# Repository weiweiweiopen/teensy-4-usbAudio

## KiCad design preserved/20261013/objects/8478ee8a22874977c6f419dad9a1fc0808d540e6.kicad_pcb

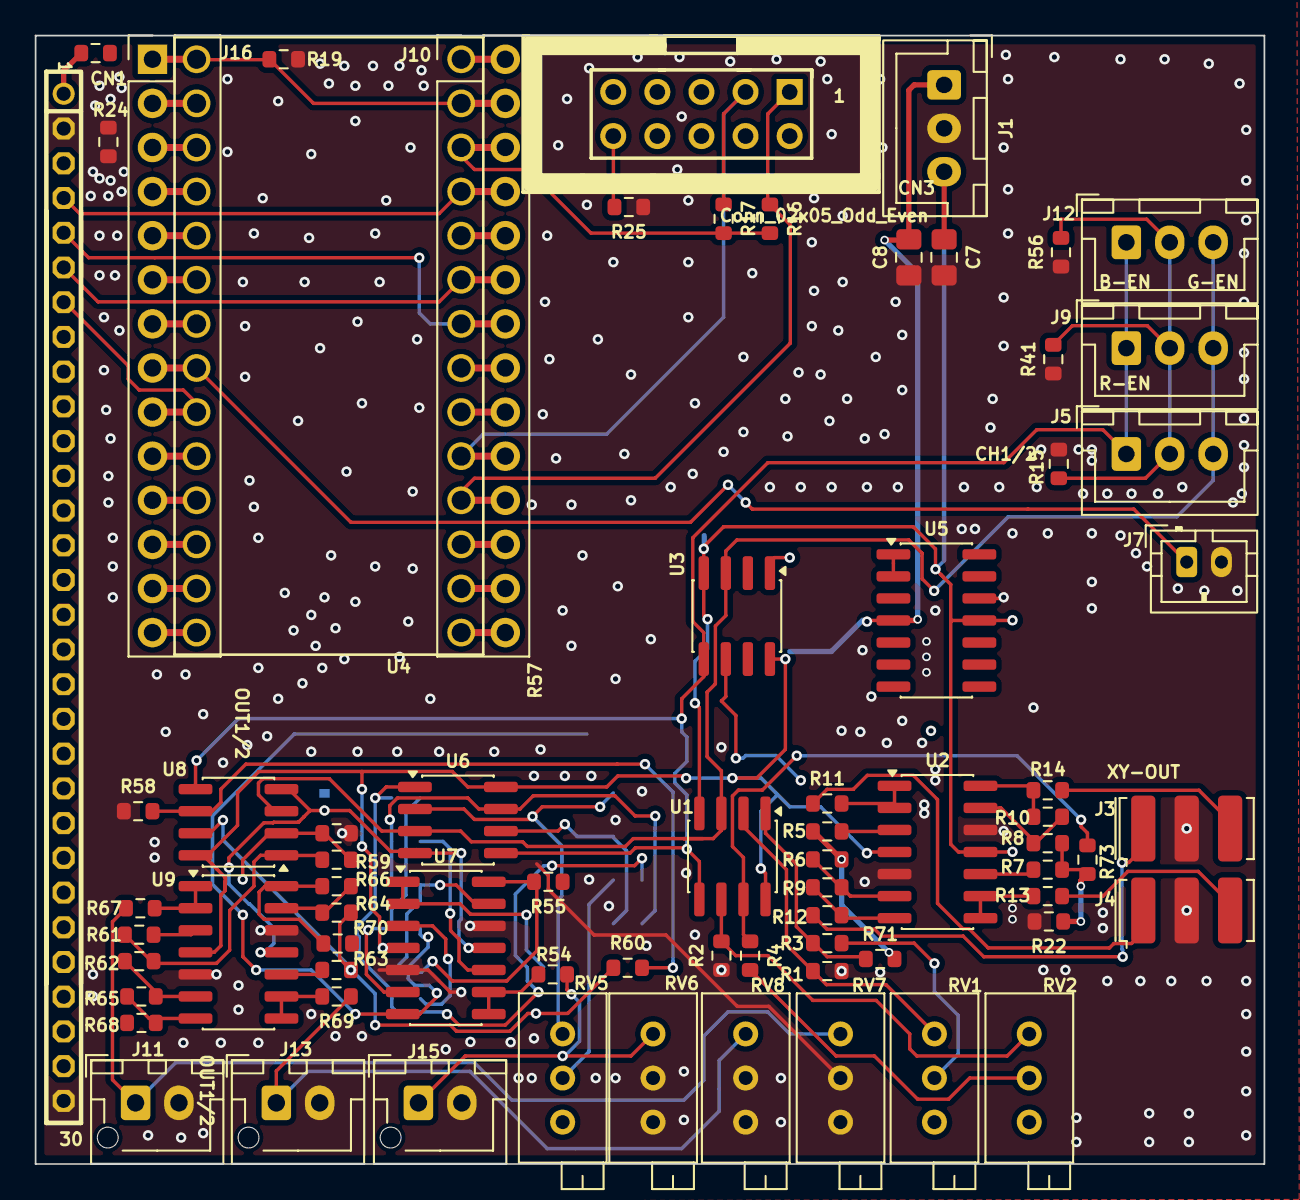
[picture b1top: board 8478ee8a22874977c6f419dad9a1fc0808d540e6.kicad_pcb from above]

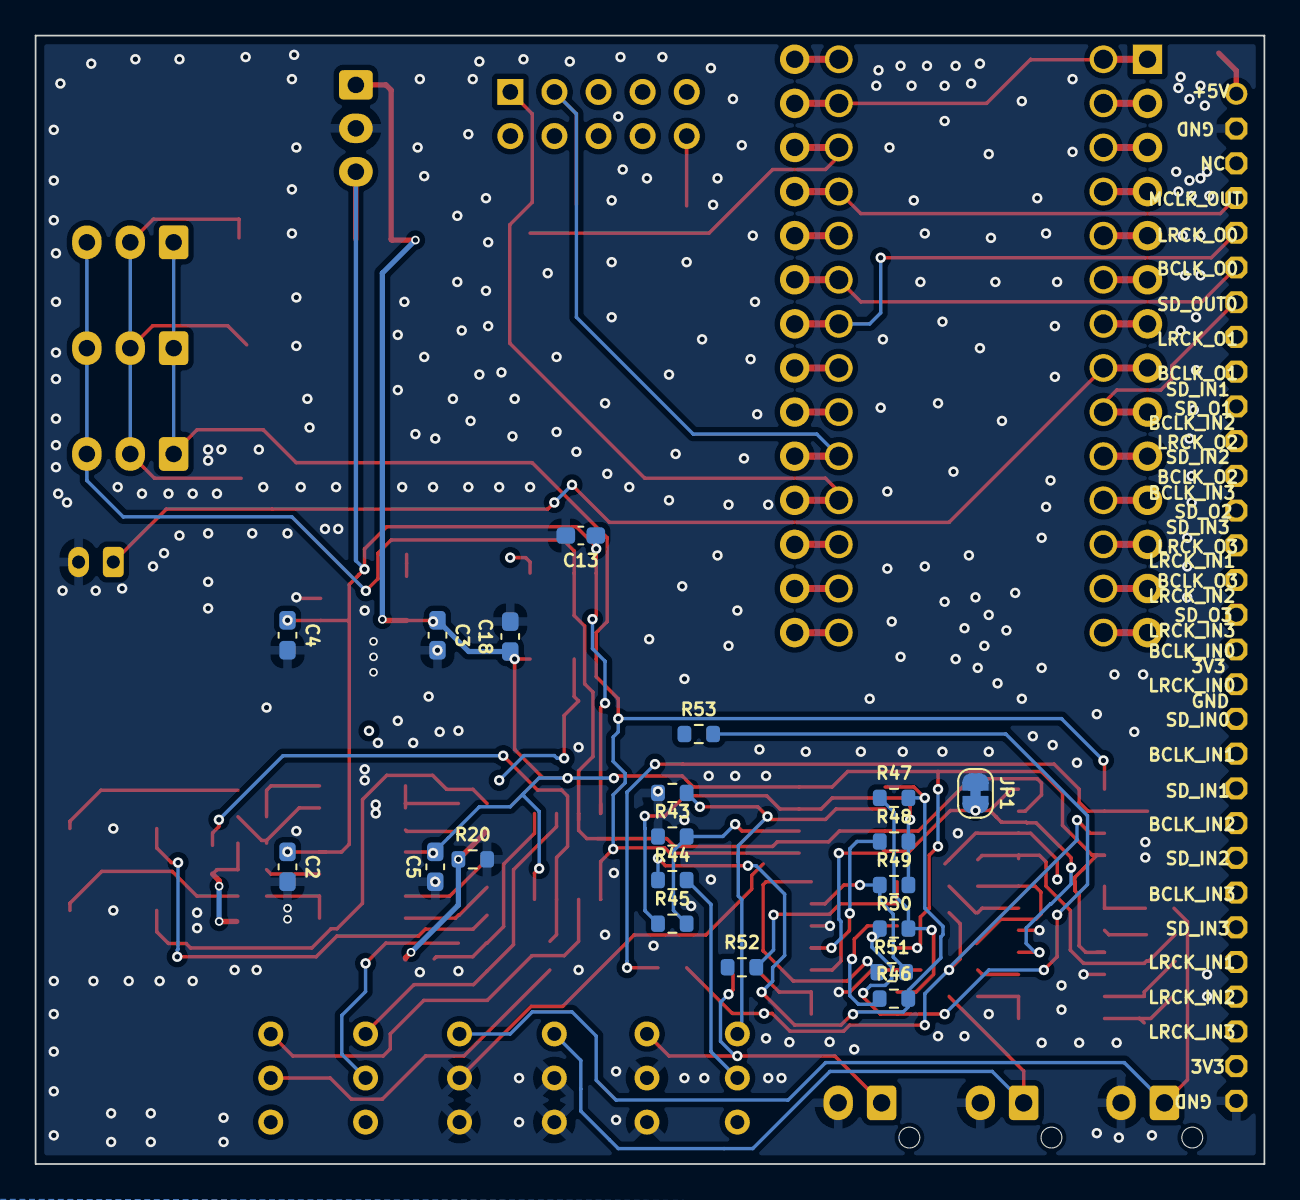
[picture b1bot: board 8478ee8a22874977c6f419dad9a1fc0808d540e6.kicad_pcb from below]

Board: 4 copper layers, 70.8 x 65.0 mm, 93 parts (20 on the bottom side), 66 nets.

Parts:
C2, C3, C4, C5, C13, C18: 0.1uF; C_0603_1608Metric_Pad1.08x0.95mm_HandSolder
C7, C8: 10uF; C_0805_2012Metric_Pad1.18x1.45mm_HandSolder
CN1: Conn_01x30_Pin; 2.0*30
CN3: Conn_02x05_Odd_Even; IDC2X5
J1, J5, J9, J12: +15 G -15; JST_XH_B3B-XH-A_1x03_P2.50mm_Vertical
J3, J4: +15 G -15; Resonator_SMD-3Pin_7.2x3.0mm
J7: 405nm; JST_PH_B2B-PH-K_1x02_P2.00mm_Vertical
J10, J16: Conn_02x14_Odd_Even; PinHeader_2x14_P2.54mm_Vertical
J11, J13, J15: Conn_01x02; JST_XH_B2B-XH-AM_1x02_P2.50mm_Vertical
JP1: Jumper_2_Bridged; SolderJumper-2_P1.3mm_Bridged_RoundedPad1.0x1.5mm
R1, R2, R5, R7, R20, R22, R42, R43, R46, R48, R54, R57, R58, R61, R63, R67, R69: 1k; R_0603_1608Metric
R3, R4, R11, R12, R13, R14, R44, R45, R59, R60: 330; R_0603_1608Metric
R6, R8, R9, R10, R47, R49, R50, R51, R62, R64, R65, R66: 22k; R_0603_1608Metric
R15, R18, R24, R25, R41, R56: 0R; R_0603_1608Metric
R16, R17: 2.2k; R_0603_1608Metric
R19: DNP; R_0603_1608Metric
R52, R53, R55, R68, R70: DNP不贴; R_0603_1608Metric
R71, R73: 1.5k; R_0603_1608Metric
RV1, RV2, RV5: 10k; Potentiometer_Bourns_3296X_Horizontal
RV6, RV7, RV8: 1k; Potentiometer_Bourns_3296X_Horizontal
U1, U3, U6, U8: TL072; SOIC-8_3.9x4.9mm_P1.27mm
U2, U5, U7, U9: TL074; SOIC-14_3.9x8.7mm_P1.27mm
U4: Teensy4.0; Teensy40

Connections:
+3.3V: R16.2, R17.2, U4.31 (3V3)
+15V: C3.1, C5.1, C8.1, C18.1, J1.1, U1.8 (V+), U2.4 (V+), U3.8 (V+), U5.4 (V+), U6.8 (V+), U7.4 (V+), U8.8 (V+), U9.4 (V+)
-15V: C2.1, C4.1, C7.1, C13.1, J1.3, U1.4 (V-), U2.11 (V-), U3.4 (V-), U5.11 (V-)
/BCLK-OUT0: CN1.6, U4.28 (21_A7_RX5_BCLK1)
/LRCK-OUT0: CN1.5, U4.27 (20_A6_TX5_LRCLK1)
/MCLK-OUT: CN1.4, U4.30 (23_A9_CRX1_MCLK1)
/SCL2_M: CN3.1, R16.1, U4.23 (16_A2_RX4_SCL1)
/SD-OUT0: CN1.7, U4.9 (7_RX2_OUT1A)
/SDA2_M: CN3.3, R17.1, U4.24 (17_A3_TX4_SDA1)
/T_GND: R19.1, U4.1 (GND), U4.32 (GND)
/VBUS: CN1.1, R18.2
/laser en: J7.1, U4.8 (6_OUT1D)
Ax_Ring_OUT: J5.1, J9.1, J12.1, U1.5 (+), U6.5 (+), U8.5 (+)
Ax_Sleeve_OUT: J5.2, J9.2, J12.2, R15.2, R41.2, R56.2
Ax_Tip_OUT: J5.3, J9.3, J12.3, U1.3 (+), U6.3 (+), U8.3 (+)
GND: C2.2, C3.2, C4.2, C5.2, C7.2, C8.2, C13.2, C18.2, CN1.2, CN1.30, J1.2, J3.2, J4.2, J7.2, J11.2, J13.2, J15.2, JP1.1 (A), R1.1, R2.1, R15.1, R19.2, R20.2, R22.2, R24.1, R24.2, R25.1, R41.1, R42.1, R43.1, R56.1, R57.1, R58.1, RV6.2, RV6.3, RV7.2, RV7.3, RV8.2, RV8.3, U2.5 (+), U2.12 (+), U7.5 (+), U7.12 (+), U9.5 (+), U9.12 (+)
unnamed: CN3.10, R25.2
unnamed: J3.1, R12.1
unnamed: J3.3, R14.1
unnamed: J4.1, R11.1
unnamed: J4.3, R13.1
unnamed: J11.1, R67.1, RV7.1
unnamed: J13.1, R69.1, RV8.1
unnamed: J15.1, R54.1, RV6.1
unnamed: JP1.2 (B), U6.4 (V-), U7.11 (V-), U8.4 (V-), U9.11 (V-)
unnamed: R3.1, R71.1, U1.1
unnamed: R3.2, RV1.2
unnamed: R4.1, R73.1, U1.7
unnamed: R4.2, RV2.2
unnamed: R10.1, R14.2, U2.14
unnamed: R9.1, R12.2, U2.7
unnamed: R5.2, R6.2, R20.1, R71.2
unnamed: R7.2, R8.2, R22.1, R73.2
unnamed: R44.1, R46.2, R47.2, U6.1
unnamed: R44.2, RV5.2
unnamed: R45.1, R48.2, R49.2, U6.7
unnamed: R50.1, R53.2, U7.7
unnamed: R51.1, R55.2, U7.14
unnamed: R59.1, R61.2, R62.2, U8.1
unnamed: R60.1, R63.2, R64.2, U8.7
unnamed: R65.1, R68.2, U9.7
unnamed: R66.1, R70.2, U9.14
unnamed: R1.2, RV1.1, U1.2 (-)
unnamed: R2.2, RV2.1, U1.6 (-)
unnamed: R5.1, U2.3 (+)
unnamed: R11.2, U2.1, U2.2 (-)
unnamed: R6.1, R9.2, U2.6 (-)
unnamed: R7.1, U2.10 (+)
unnamed: R13.2, U2.8, U2.9 (-)
unnamed: R8.1, R10.2, U2.13 (-)
unnamed: R42.2, RV5.1, U6.2 (-)
unnamed: R43.2, R45.2, U6.6 (-)
unnamed: R46.1, U7.3 (+)
unnamed: R52.2, U7.1, U7.2 (-)
unnamed: R47.1, R50.2, U7.6 (-)
unnamed: R48.1, U7.10 (+)
unnamed: R54.2, U7.8, U7.9 (-)
unnamed: R49.1, R51.2, U7.13 (-)
unnamed: R57.2, R59.2, U8.2 (-)
unnamed: R58.2, R60.2, U8.6 (-)
unnamed: R61.1, U9.3 (+)
unnamed: R67.2, U9.1, U9.2 (-)
unnamed: R62.1, R65.2, U9.6 (-)
unnamed: R63.1, U9.10 (+)
unnamed: R69.2, U9.8, U9.9 (-)
unnamed: R64.1, R66.2, U9.13 (-)

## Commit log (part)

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2026-03-25 Add complete KiCad starter package for 6/8 CS42448 laser DAC
